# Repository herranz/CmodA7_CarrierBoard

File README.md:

# CMOD A7 Carrier Board
Carrier board for the CmodA7 

Inline-style:

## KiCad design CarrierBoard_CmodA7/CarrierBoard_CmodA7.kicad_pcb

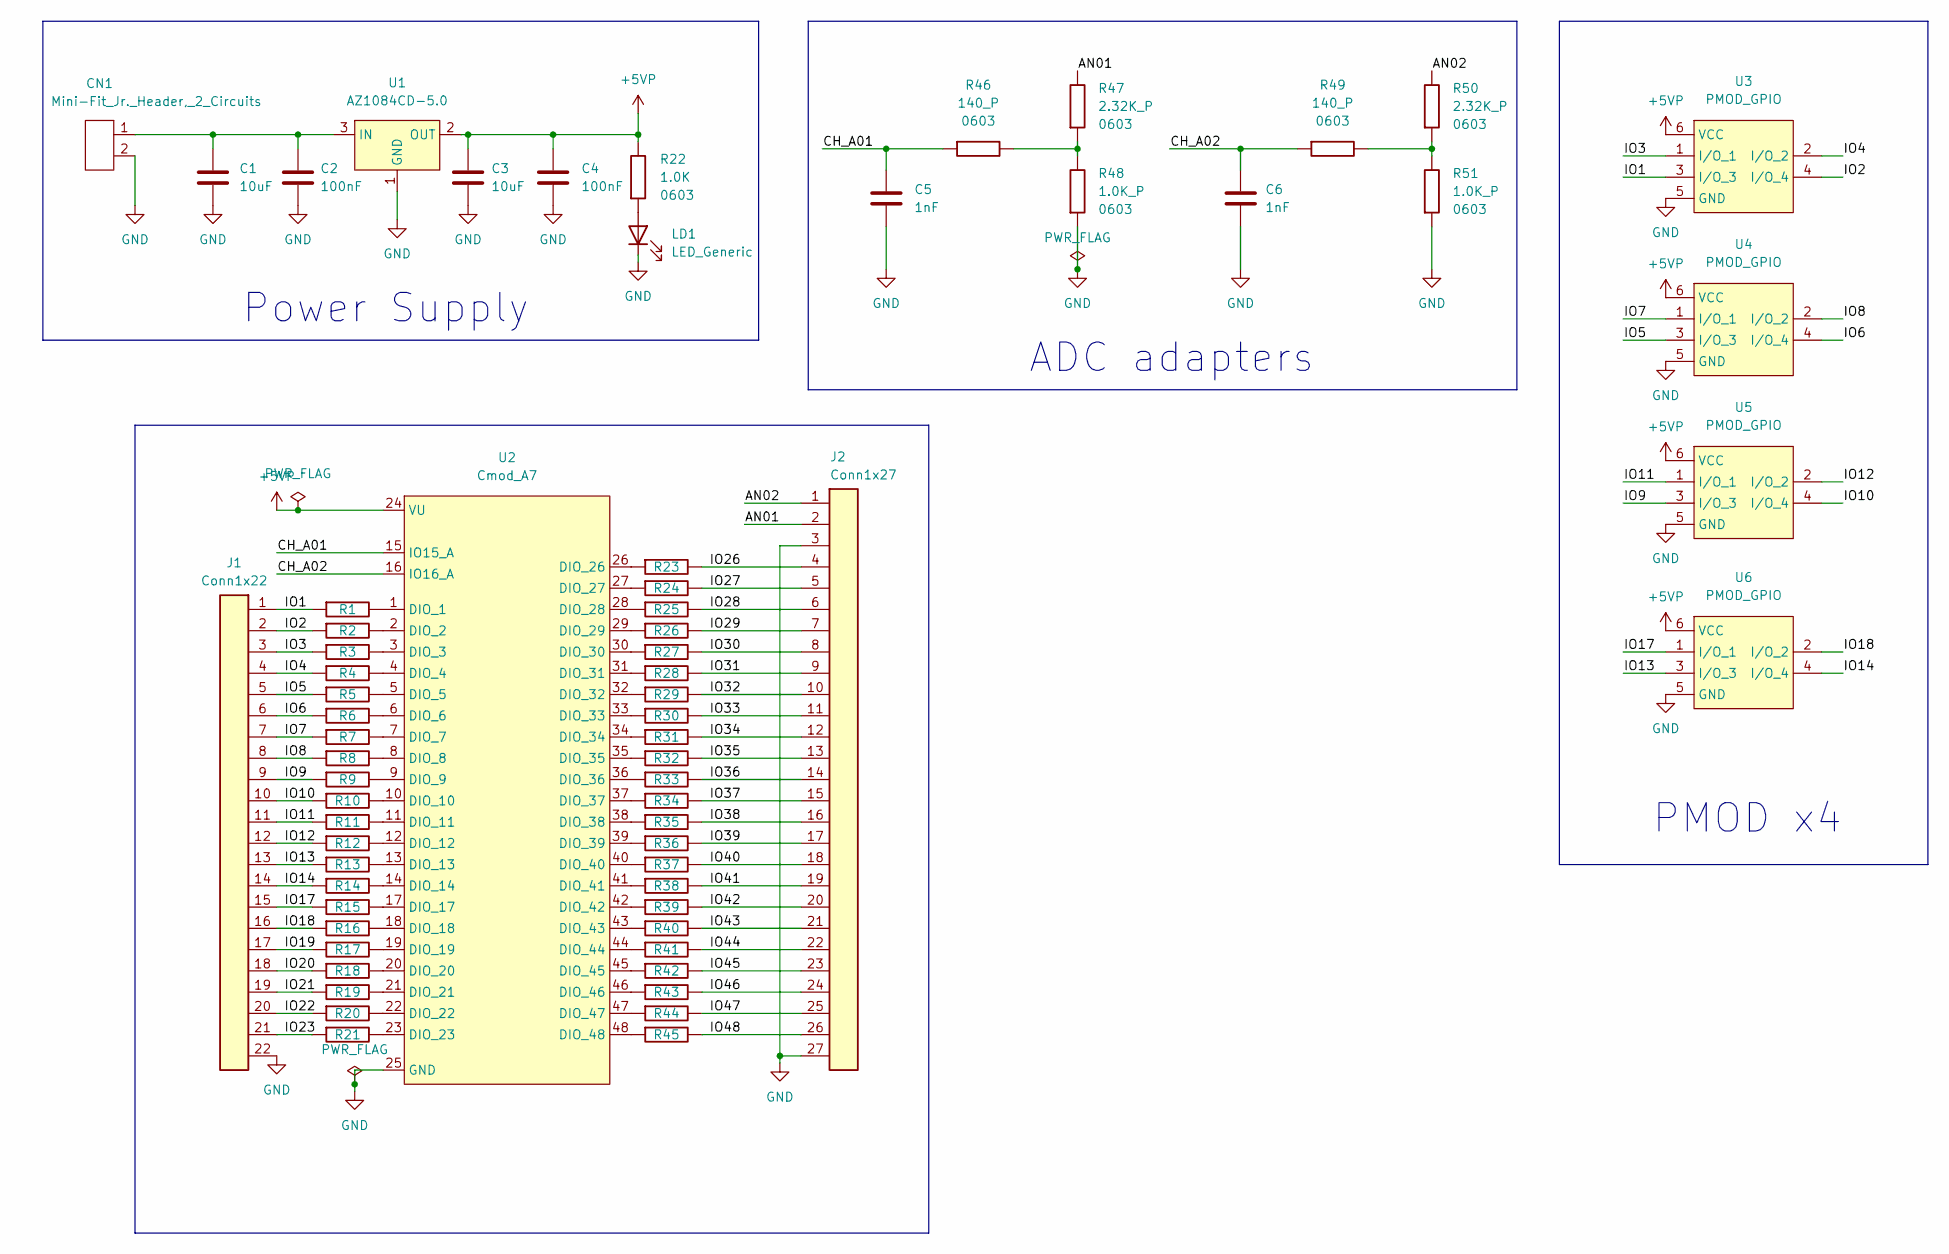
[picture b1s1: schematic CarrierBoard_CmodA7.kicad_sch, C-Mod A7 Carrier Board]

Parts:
C1, C3: 10uF; C_0805_2012Metric
C2, C4: 100nF; C_0805_2012Metric
C5, C6: 1nF; C_0603_1608Metric
CN1: Mini-Fit_Jr._Header,_2_Circuits; Mini-Fit Jr. Header, 2 Circuits
J1: Conn1x22; PinSocket_1x22_P2.54mm_Vertical
J2: Conn1x27; PinSocket_1x27_P2.54mm_Vertical
LD1: LED_Generic; LED_0603_1608Metric_Pad1.05x0.95mm_HandSolder
R1, R2, R3, R4, R5, R6, R7, R8, R9, R10, R11, R12, R13, R14, R15, R16, R17, R18, R19, R20, R21, R22, R23, R24, R25, R26, R27, R28, R29, R30, R31, R32, R33, R34, R35, R36, R37, R38, R39, R40, R41, R42, R43, R44, R45: 1.0K; R_0603_1608Metric
R46, R49: 140_P; R_0603_1608Metric; PartNum1 RN73H1JTTD1400F50
R47, R50: 2.32K_P; R_0603_1608Metric
R48, R51: 1.0K_P; R_0603_1608Metric
U1: AZ1084CD-5.0; DPAK457P1010X238-3N
U2: Cmod_A7; CmodA7
U3, U4, U5, U6: PMOD_GPIO; PinSocket_2x03_P2.54mm_Horizontal

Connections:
+5VP: C3.1, C4.1, R22.2, U1.2 (OUT), U2.24 (VU), U3.6 (VCC), U4.6 (VCC), U5.6 (VCC), U6.6 (VCC)
/AN01: J2.2, R47.2
/AN02: J2.1, R50.2
/CH_A01: C5.1, R46.1, U2.15 (IO15_A)
/CH_A02: C6.1, R49.1, U2.16 (IO16_A)
/IO1: J1.1, R1.1, U3.3 (I/O_3)
/IO2: J1.2, R2.1, U3.4 (I/O_4)
/IO3: J1.3, R3.1, U3.1 (I/O_1)
/IO4: J1.4, R4.1, U3.2 (I/O_2)
/IO5: J1.5, R5.1, U4.3 (I/O_3)
/IO6: J1.6, R6.1, U4.4 (I/O_4)
/IO7: J1.7, R7.1, U4.1 (I/O_1)
/IO8: J1.8, R8.1, U4.2 (I/O_2)
/IO9: J1.9, R9.1, U5.3 (I/O_3)
/IO10: J1.10, R10.1, U5.4 (I/O_4)
/IO11: J1.11, R11.1, U5.1 (I/O_1)
/IO12: J1.12, R12.1, U5.2 (I/O_2)
/IO13: J1.13, R13.1, U6.3 (I/O_3)
/IO14: J1.14, R14.1, U6.4 (I/O_4)
/IO17: J1.15, R15.1, U6.1 (I/O_1)
/IO18: J1.16, R16.1, U6.2 (I/O_2)
/IO19: J1.17, R17.1
/IO20: J1.18, R18.1
/IO21: J1.19, R19.1
/IO22: J1.20, R20.1
/IO23: J1.21, R21.1
/IO26: J2.4, R23.2
/IO27: J2.5, R24.2
/IO28: J2.6, R25.2
/IO29: J2.7, R26.2
/IO30: J2.8, R27.2
/IO31: J2.9, R28.2
/IO32: J2.10, R29.2
/IO33: J2.11, R30.2
/IO34: J2.12, R31.2
/IO35: J2.13, R32.2
/IO36: J2.14, R33.2
/IO37: J2.15, R34.2
/IO38: J2.16, R35.2
/IO39: J2.17, R36.2
/IO40: J2.18, R37.2
/IO41: J2.19, R38.2
/IO42: J2.20, R39.2
/IO43: J2.21, R40.2
/IO44: J2.22, R41.2
/IO45: J2.23, R42.2
/IO46: J2.24, R43.2
/IO47: J2.25, R44.2
/IO48: J2.26, R45.2
GND: C1.2, C2.2, C3.2, C4.2, C5.2, C6.2, CN1.2, J1.22, J2.3, J2.27, LD1.2 (K), R48.1, R51.1, U1.1 (GND), U2.25 (GND), U3.5 (GND), U4.5 (GND), U5.5 (GND), U6.5 (GND)
unnamed: C1.1, C2.1, CN1.1, U1.3 (IN)
unnamed: LD1.1 (A), R22.1
unnamed: R1.2, U2.1 (DIO_1)
unnamed: R2.2, U2.2 (DIO_2)
unnamed: R3.2, U2.3 (DIO_3)
unnamed: R4.2, U2.4 (DIO_4)
unnamed: R5.2, U2.5 (DIO_5)
unnamed: R6.2, U2.6 (DIO_6)
unnamed: R7.2, U2.7 (DIO_7)
unnamed: R8.2, U2.8 (DIO_8)
unnamed: R9.2, U2.9 (DIO_9)
unnamed: R10.2, U2.10 (DIO_10)
unnamed: R11.2, U2.11 (DIO_11)
unnamed: R12.2, U2.12 (DIO_12)
unnamed: R13.2, U2.13 (DIO_13)
unnamed: R14.2, U2.14 (DIO_14)
unnamed: R15.2, U2.17 (DIO_17)
unnamed: R16.2, U2.18 (DIO_18)
unnamed: R17.2, U2.19 (DIO_19)
unnamed: R18.2, U2.20 (DIO_20)
unnamed: R19.2, U2.21 (DIO_21)
unnamed: R20.2, U2.22 (DIO_22)
unnamed: R21.2, U2.23 (DIO_23)
unnamed: R23.1, U2.26 (DIO_26)
unnamed: R24.1, U2.27 (DIO_27)
unnamed: R25.1, U2.28 (DIO_28)
unnamed: R26.1, U2.29 (DIO_29)
unnamed: R27.1, U2.30 (DIO_30)
unnamed: R28.1, U2.31 (DIO_31)
unnamed: R29.1, U2.32 (DIO_32)
unnamed: R30.1, U2.33 (DIO_33)
unnamed: R31.1, U2.34 (DIO_34)
unnamed: R32.1, U2.35 (DIO_35)
unnamed: R33.1, U2.36 (DIO_36)
unnamed: R34.1, U2.37 (DIO_37)
unnamed: R35.1, U2.38 (DIO_38)
unnamed: R36.1, U2.39 (DIO_39)
unnamed: R37.1, U2.40 (DIO_40)
unnamed: R38.1, U2.41 (DIO_41)
unnamed: R39.1, U2.42 (DIO_42)
unnamed: R40.1, U2.43 (DIO_43)
unnamed: R41.1, U2.44 (DIO_44)
unnamed: R42.1, U2.45 (DIO_45)
unnamed: R43.1, U2.46 (DIO_46)
unnamed: R44.1, U2.47 (DIO_47)
unnamed: R45.1, U2.48 (DIO_48)
unnamed: R46.2, R47.1, R48.2
unnamed: R49.2, R50.1, R51.2

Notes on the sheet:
Power Supply
PMOD x4
ADC adapters

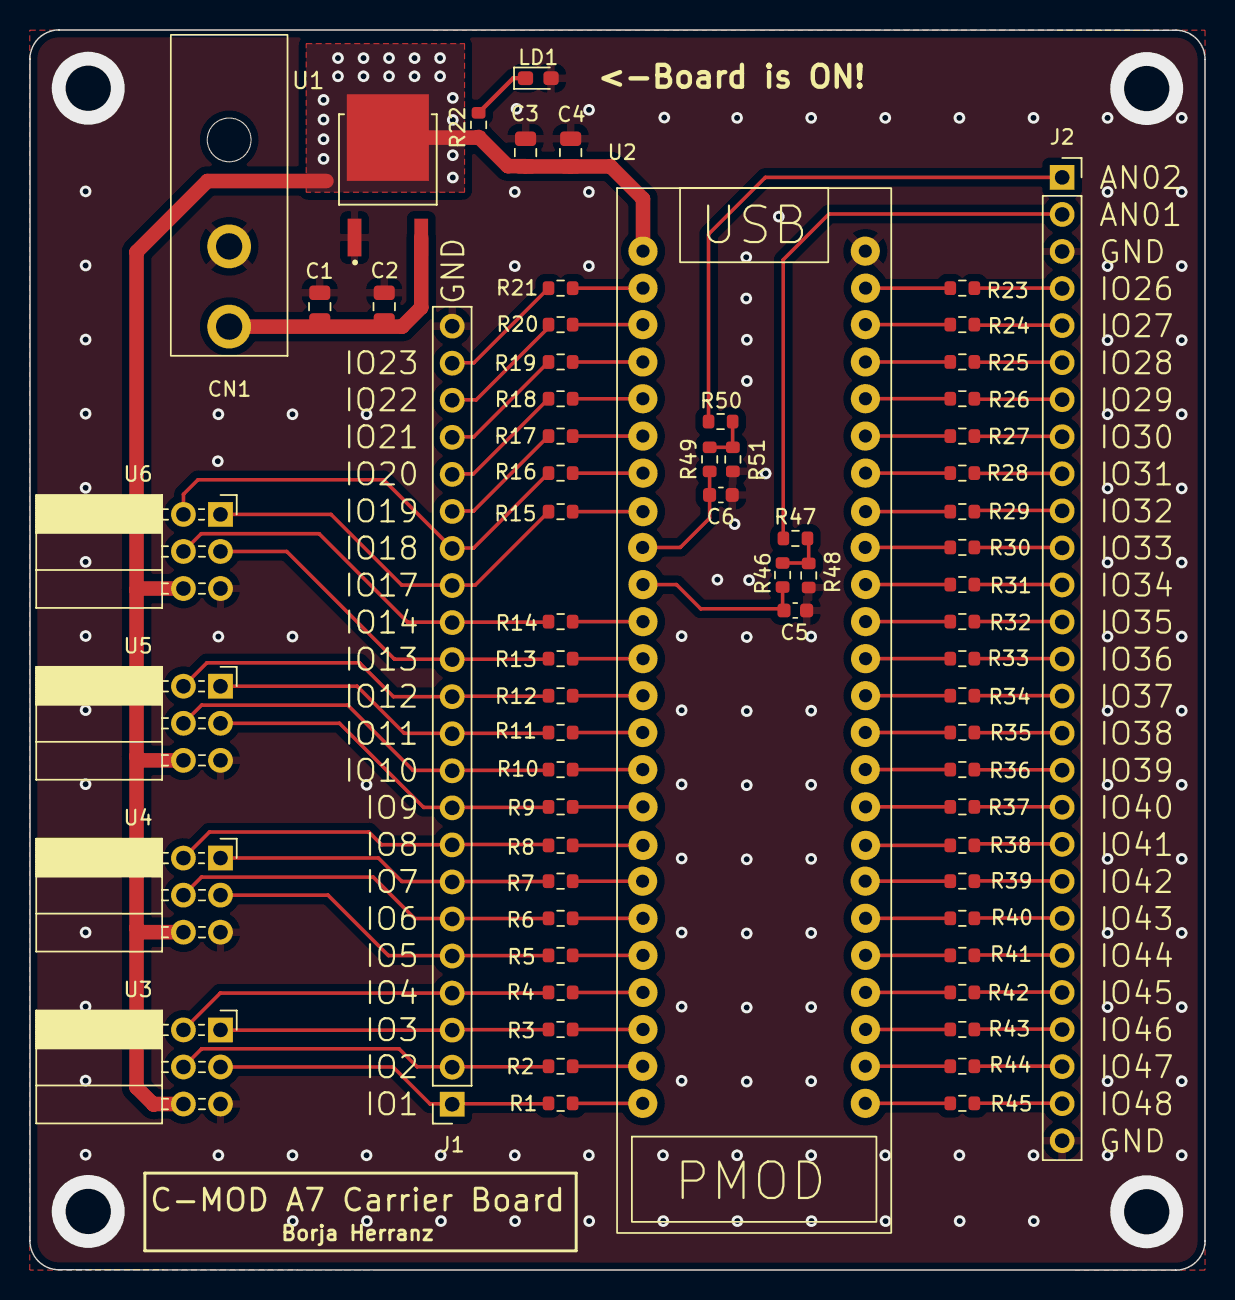
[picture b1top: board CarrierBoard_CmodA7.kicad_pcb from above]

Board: 2 copper layers, 80.6 x 85.0 mm, 67 parts (0 on the bottom side), 98 nets.

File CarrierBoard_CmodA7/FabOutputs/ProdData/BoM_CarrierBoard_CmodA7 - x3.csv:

Id,Designator,Package,Quantity,Designation,LCSC
1,"R46,R49",R_0603_1608Metric,6,140_P,C203298
2,"U3,U5,U4,U6",PinSocket_2x03_P2.54mm_Horizontal,12,PMOD_GPIO,C920880
3,"R21,R28,R9,R2,R14,R23,R3,R41,R4,R43,R40,R8,R13,R36,R27,R22,R19,R25,R15,R16,R31,R35,R20,R38,R29,R34,R32,R12,R26,R10,R6,R39,R45,R33,R11,R17,R18,R44,R1,R37,R7,R30,R5,R24,R42",R_0603_1608Metric,135,1.0K,C844746
4,LD1,LED_0603_1608Metric_Pad1.05x0.95mm_HandSolder,3,LED_Generic,C241893
5,U1,DPAK457P1010X238-3N,3,AZ1084CD-5.0,C2980701
6,J1,PinSocket_1x22_P2.54mm_Vertical,3,Conn1x22,NA
7,"R51,R48",R_0603_1608Metric,6,1.0K_P,C719293
8,"C6,C5",C_0603_1608Metric,6,1nF,C696365
9,"C4,C2",C_0805_2012Metric,6,100nF,C695378
10,U2,CmodA7,3,Cmod_A7,NA
11,"R47,R50",R_0603_1608Metric,6,2.32K_P,NA
12,"C1,C3",C_0805_2012Metric,6,10uF,C342723
13,J2,PinSocket_1x27_P2.54mm_Vertical,3,Conn1x27,NA
14,CN1,"Mini-Fit Jr. Header, 2 Circuits",3,"Mini-Fit_Jr._Header,_2_Circuits",NA

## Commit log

2022-03-13 Creacion del proyecto
2022-03-14 añadidas current limiter resistors
2022-03-18 Añadidos conectores PMOD
2022-03-22 añadido red ADC
2022-03-25 esquema ordenado
2022-03-27 añadido condensadores power supply
2022-06-08 Arreglado el circuto del ADC
2022-06-08 Arreglado Tira pines 1x22 a 1x21, cambiado el nivel de prioridad de los planos de cobre
2022-06-26 arreglado divisor de tension y filtro del ADC.
2022-06-26 Retoques en la PCB, añadido info sobre el proyecto
2022-06-27 Update readme.md
    Añadida imagen
2022-06-27 añadido part numbers LSCS para prototipado en JLCPCB
2022-06-27 gerbers regenerados
2022-06-27 modificado el gitignore, añadido BoM
2022-07-07 Arreglado BoM y esquemas
